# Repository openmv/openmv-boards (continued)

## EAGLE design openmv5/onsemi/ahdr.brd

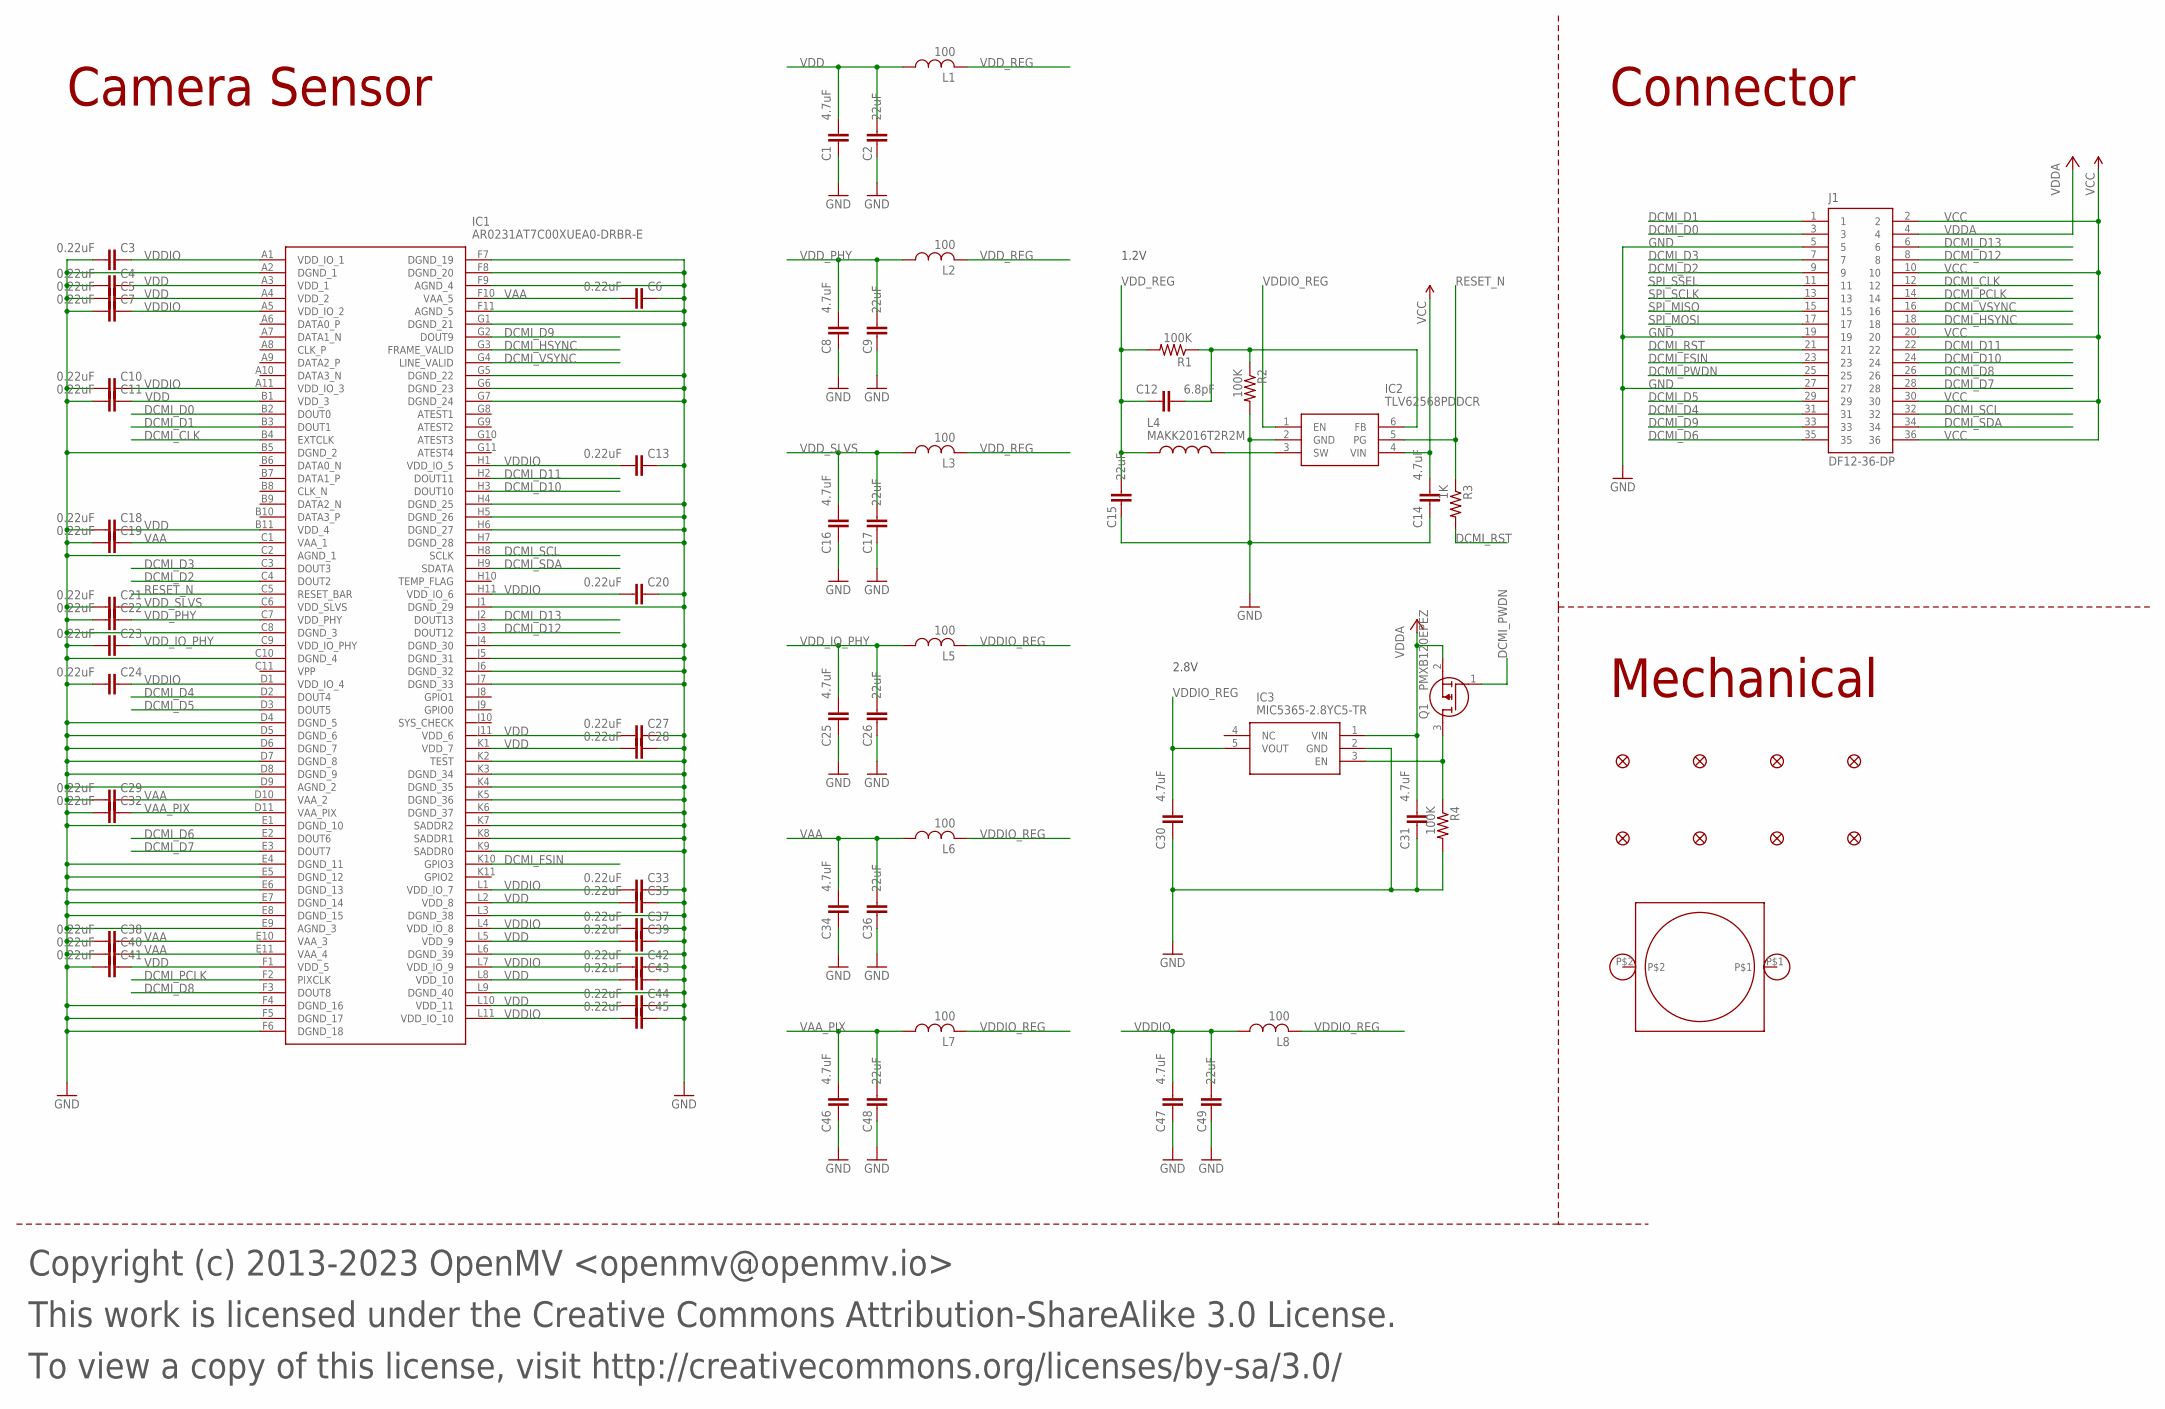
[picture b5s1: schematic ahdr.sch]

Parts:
C1, C8, C14, C16, C25, C30, C31, C34, C46, C47: 4.7uF; 0402; MPN JMK105BBJ475MV-F
C2, C9, C15, C17, C26, C36, C48, C49: 22uF; 0805; MPN CL21A226MQQNNNE
C3, C4, C5, C6, C7, C10, C11, C13, C18, C19, C20, C21, C22, C23, C24, C27, C28, C29, C32, C33, C35, C37, C38, C39, C40, C41, C42, C43, C44, C45: 0.22uF; C0201; MPN GRM033R60J224ME15D
C12: 6.8pF; 0402; MPN GRM1555C1H6R8DA01D
FD1, FD2, FD3, FD4, FD5, FD6, FD7, FD8: FIDUCIAL1X2; FIDUCIAL-1X2
H1: LENSMOUNT20MM; LENSMOUNT-20MM
IC1: AR0231AT7C00XUEA0-DRBR-E; BGA121C80P11X11_1100X1000X155; MPN AR0231AT7C00XUEA0-DPBR
IC2: TLV62568PDDCR; SOT95P280X110-6N; MPN TLV62568PDDCR
IC3: MIC5365-2.8YC5-TR; SOT65P210X110-5N; MPN MIC5365-2.8YC5-TR
J1: DF12-36-DP; MPN DF12NB(3.0)-36DP-0.5V(51)
L1, L2, L3, L5, L6, L7, L8: 100; 0402; MPN MFBM1V1005-101-R
L4: MAKK2016T2R2M; INDC2016X100N; MPN MAKK2016T2R2M
Q1: PMXB120EPEZ; MPN PMXB120EPEZ
R1, R2, R4: 100K; R0402; MPN AC0402FR-07100KL
R3: 1K; R0402; MPN CRCW04021K00FKEDC

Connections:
DCMI_CLK: IC1.B4 (EXTCLK), J1.12
DCMI_D0: IC1.B2 (DOUT0), J1.3
DCMI_D1: IC1.B3 (DOUT1), J1.1
DCMI_D2: IC1.C4 (DOUT2), J1.9
DCMI_D3: IC1.C3 (DOUT3), J1.7
DCMI_D4: IC1.D2 (DOUT4), J1.31
DCMI_D5: IC1.D3 (DOUT5), J1.29
DCMI_D6: IC1.E2 (DOUT6), J1.35
DCMI_D7: IC1.E3 (DOUT7), J1.28
DCMI_D8: IC1.F3 (DOUT8), J1.26
DCMI_D9: IC1.G2 (DOUT9), J1.33
DCMI_D10: IC1.H3 (DOUT10), J1.24
DCMI_D11: IC1.H2 (DOUT11), J1.22
DCMI_D12: IC1.J3 (DOUT12), J1.8
DCMI_D13: IC1.J2 (DOUT13), J1.6
DCMI_FSIN: IC1.K10 (GPIO3), J1.23
DCMI_HSYNC: IC1.G3 (FRAME_VALID), J1.18
DCMI_PCLK: IC1.F2 (PIXCLK), J1.14
DCMI_PWDN: J1.25, Q1.1 (G)
DCMI_PWDN_INT: IC3.3 (EN), Q1.3 (D), R4.1
DCMI_RST: J1.21, R3.2
DCMI_SCL: IC1.H8 (SCLK), J1.32
DCMI_SDA: IC1.H9 (SDATA), J1.34
DCMI_VSYNC: IC1.G4 (LINE_VALID), J1.16
FB: C12.2, IC2.6 (FB), R1.1, R2.1
GND: C1.1, C2.1, C3.2, C4.2, C5.2, C6.1, C7.2, C8.1, C9.1, C10.2, C11.2, C13.1, C14.1, C15.1, C16.1, C17.1, C18.2, C19.2, C20.1, C21.2, C22.2, C23.2, C24.2, C25.1, C26.1, C27.1, C28.1, C29.2, C30.1, C31.1, C32.2, C33.1, C34.1, C35.1, C36.1, C37.1, C38.2, C39.1, C40.2, C41.2, C42.1, C43.1, C44.1, C45.1, C46.1, C47.1, C48.1, C49.1, IC1.A2 (DGND_1), IC1.B5 (DGND_2), IC1.C2 (AGND_1), IC1.C8 (DGND_3), IC1.C10 (DGND_4), IC1.D4 (DGND_5), IC1.D5 (DGND_6), IC1.D6 (DGND_7), IC1.D7 (DGND_8), IC1.D8 (DGND_9), IC1.D9 (AGND_2), IC1.E1 (DGND_10), IC1.E4 (DGND_11), IC1.E5 (DGND_12), IC1.E6 (DGND_13), IC1.E7 (DGND_14), IC1.E8 (DGND_15), IC1.E9 (AGND_3), IC1.F4 (DGND_16), IC1.F5 (DGND_17), IC1.F6 (DGND_18), IC1.F7 (DGND_19), IC1.F8 (DGND_20), IC1.F9 (AGND_4), IC1.F11 (AGND_5), IC1.G1 (DGND_21), IC1.G5 (DGND_22), IC1.G6 (DGND_23), IC1.G7 (DGND_24), IC1.H4 (DGND_25), IC1.H5 (DGND_26), IC1.H6 (DGND_27), IC1.H7 (DGND_28), IC1.J1 (DGND_29), IC1.J4 (DGND_30), IC1.J5 (DGND_31), IC1.J6 (DGND_32), IC1.J7 (DGND_33), IC1.K2 (TEST), IC1.K3 (DGND_34), IC1.K4 (DGND_35), IC1.K5 (DGND_36), IC1.K6 (DGND_37), IC1.K7 (SADDR2), IC1.K8 (SADDR1), IC1.K9 (SADDR0), IC1.L3 (DGND_38), IC1.L6 (DGND_39), IC1.L9 (DGND_40), IC2.2 (GND), IC3.2 (GND), J1.5, J1.19, J1.27, R2.2, R4.2
RESET_N: IC1.C5 (RESET_BAR), IC2.5 (PG), R3.1
SPI_MISO: J1.15
SPI_MOSI: J1.17
SPI_SCLK: J1.13
SPI_SSEL: J1.11
SW: IC2.3 (SW), L4.2
VAA: C6.2, C19.1, C29.1, C34.2, C36.2, C38.1, C40.1, IC1.C1 (VAA_1), IC1.D10 (VAA_2), IC1.E10 (VAA_3), IC1.E11 (VAA_4), IC1.F10 (VAA_5), L6.1
VAA_PIX: C32.1, C46.2, C48.2, IC1.D11 (VAA_PIX), L7.1
VCC: C14.2, IC2.4 (VIN), J1.2, J1.10, J1.20, J1.30, J1.36
VDD: C1.2, C2.2, C4.1, C5.1, C11.1, C18.1, C27.2, C28.2, C35.2, C39.2, C41.1, C43.2, C44.2, IC1.A3 (VDD_1), IC1.A4 (VDD_2), IC1.B1 (VDD_3), IC1.B11 (VDD_4), IC1.F1 (VDD_5), IC1.J11 (VDD_6), IC1.K1 (VDD_7), IC1.L2 (VDD_8), IC1.L5 (VDD_9), IC1.L8 (VDD_10), IC1.L10 (VDD_11), L1.1
VDDA: C31.2, IC3.1 (VIN), J1.4, Q1.2 (S)
VDDIO: C3.1, C7.1, C10.1, C13.2, C20.2, C24.1, C33.2, C37.2, C42.2, C45.2, C47.2, C49.2, IC1.A1 (VDD_IO_1), IC1.A5 (VDD_IO_2), IC1.A11 (VDD_IO_3), IC1.D1 (VDD_IO_4), IC1.H1 (VDD_IO_5), IC1.H11 (VDD_IO_6), IC1.L1 (VDD_IO_7), IC1.L4 (VDD_IO_8), IC1.L7 (VDD_IO_9), IC1.L11 (VDD_IO_10), L8.1
VDDIO_REG: C30.2, IC2.1 (EN), IC3.5 (VOUT), L5.2, L6.2, L7.2, L8.2
VDD_IO_PHY: C23.1, C25.2, C26.2, IC1.C9 (VDD_IO_PHY), L5.1
VDD_PHY: C8.2, C9.2, C22.1, IC1.C7 (VDD_PHY), L2.1
VDD_REG: C12.1, C15.2, L1.2, L2.2, L3.2, L4.1, R1.2
VDD_SLVS: C16.2, C17.2, C21.1, IC1.C6 (VDD_SLVS), L3.1

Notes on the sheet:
Copyright (c) 2013-2023 OpenMV <openmv@openmv.io>
This work is licensed under the Creative Commons Attribution-ShareAlike 3.0 License.
To view a copy of this license, visit http://creativecommons.org/licenses/by-sa/3.0/
Camera Sensor
Mechanical
Connector
1.2V
2.8V

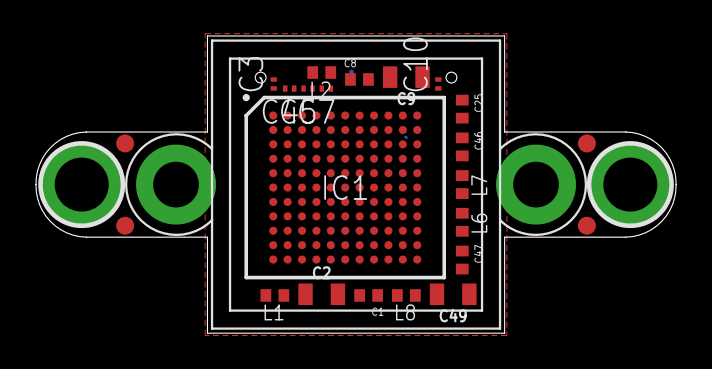
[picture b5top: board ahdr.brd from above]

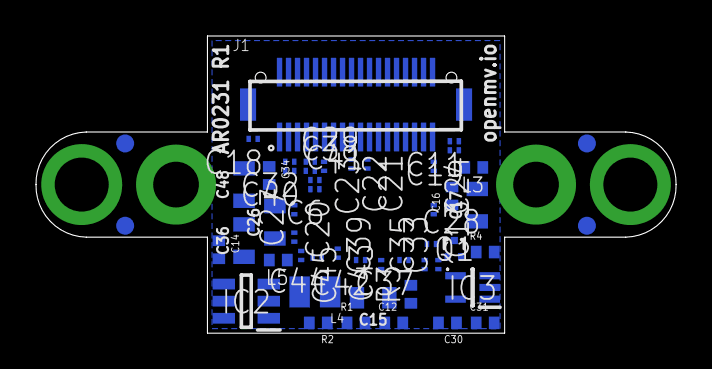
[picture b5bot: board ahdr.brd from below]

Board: 6 copper layers, 35.6 x 16.5 mm, 75 parts (51 on the bottom side), 39 nets.

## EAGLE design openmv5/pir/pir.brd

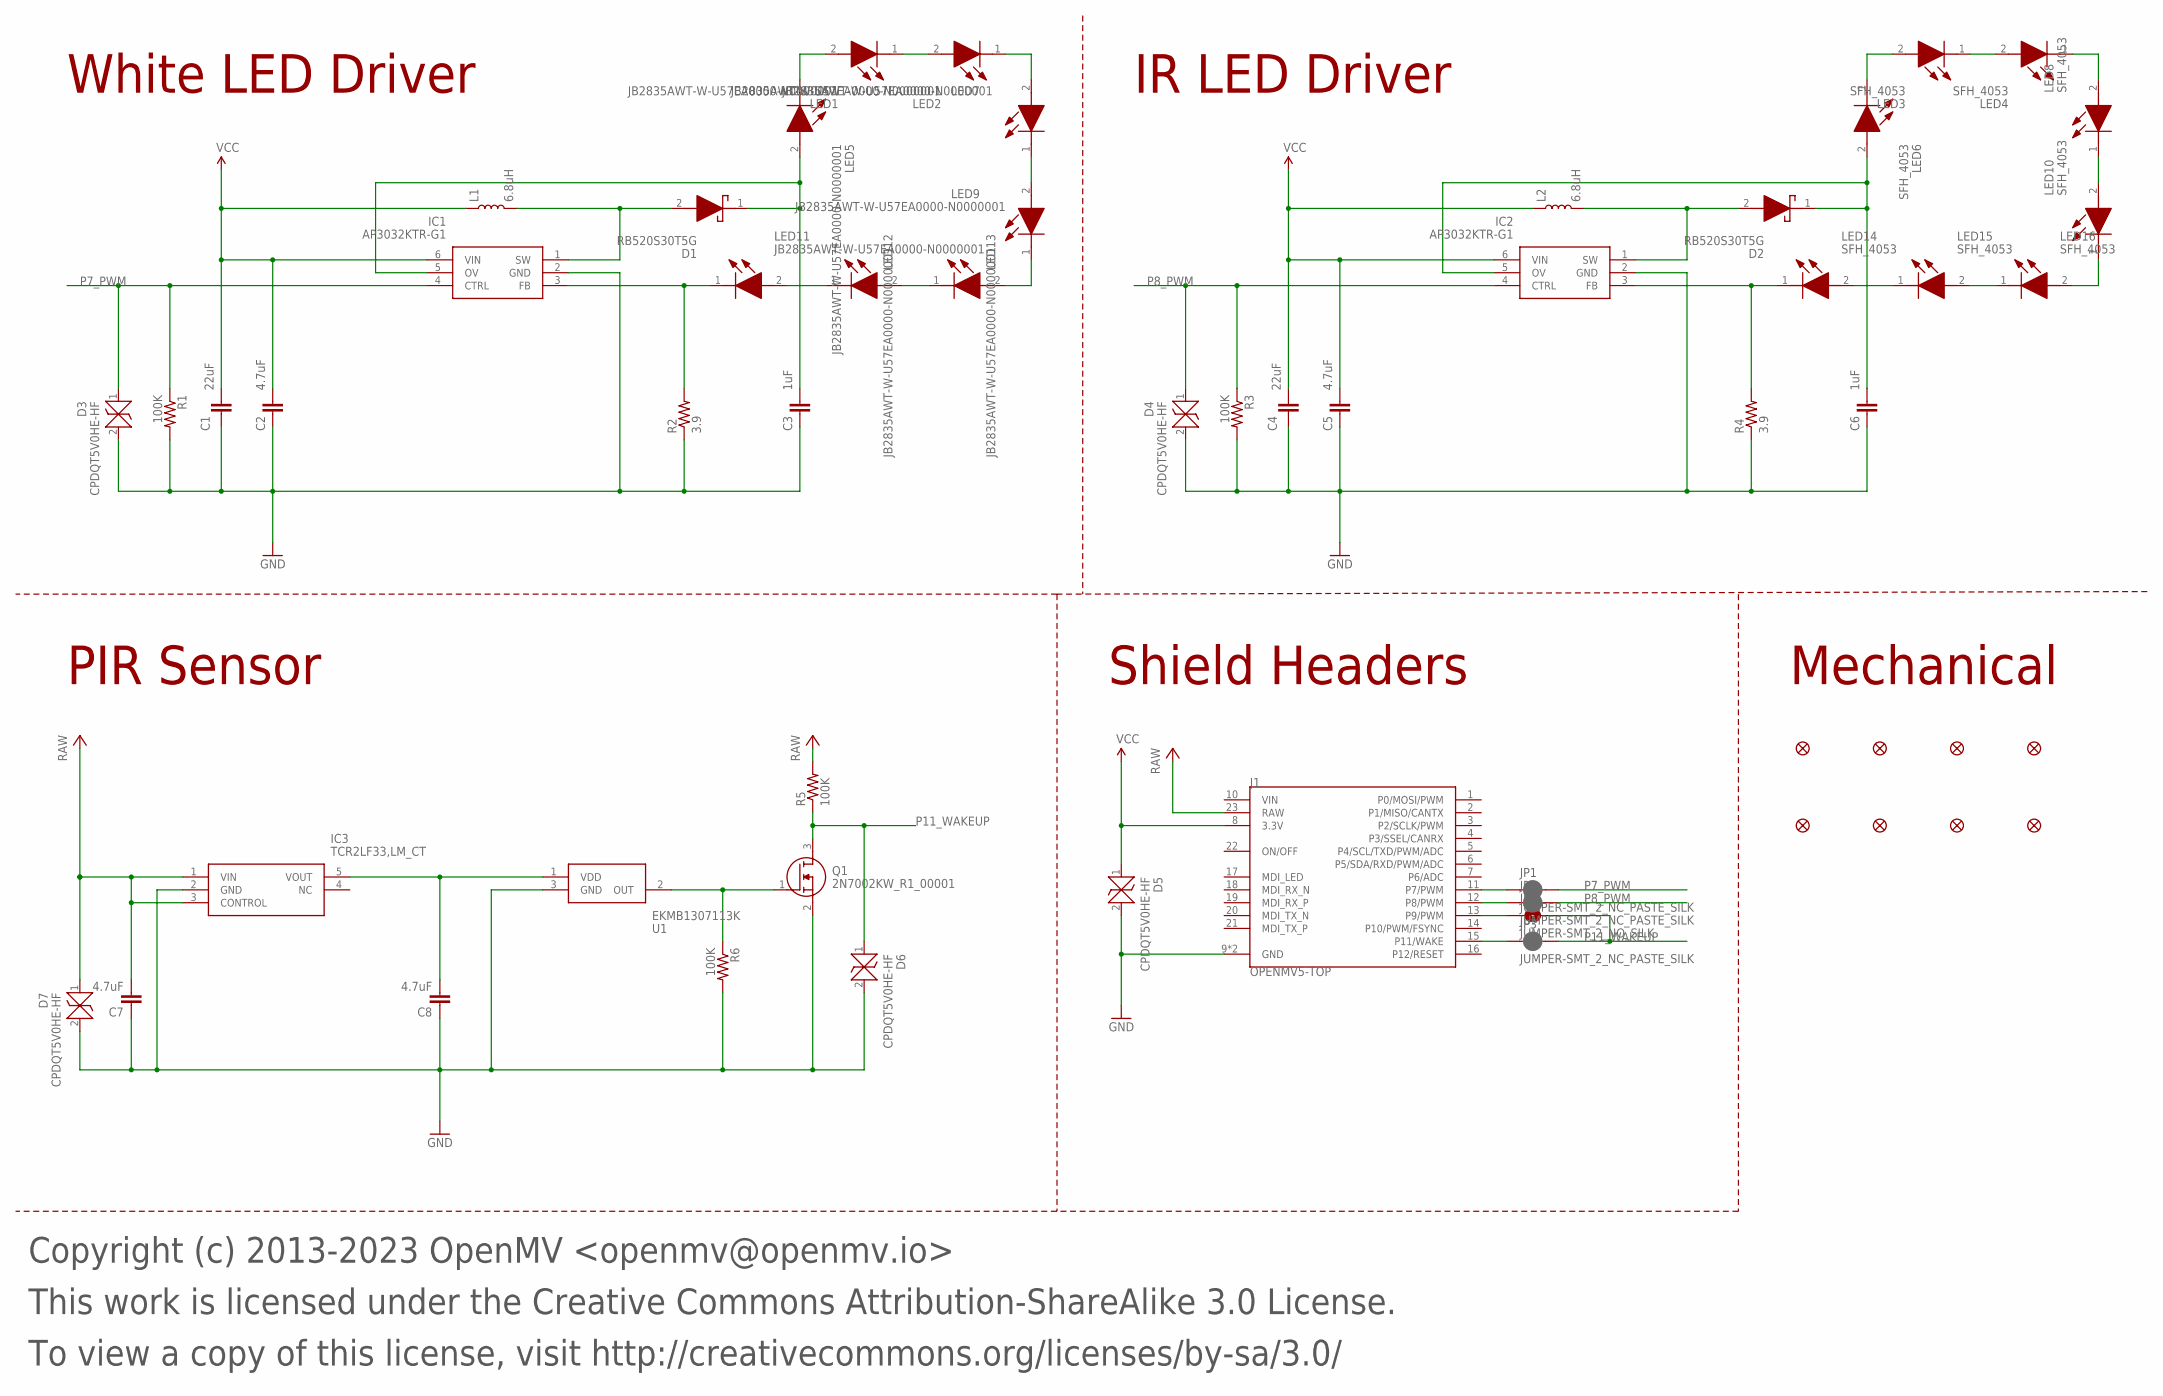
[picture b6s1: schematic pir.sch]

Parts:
C1, C4: 22uF; 0805; MPN CL21A226MQQNNNE
C2, C5, C7, C8: 4.7uF; 0402-CAP; MPN JMK105BBJ475MV-F
C3, C6: 1uF; 0402-CAP; MPN GRM155R61H105KE05D
D1, D2: RB520S30T5G; SODFL1608X70N; MPN RB520S30T5G
D3, D4, D5, D6, D7: CPDQT5V0HE-HF; CPDQT5V0HEHF; MPN CPDQT5V0HE-HF
FD1, FD2, FD3, FD4, FD5, FD6, FD7, FD8: FIDUCIAL1X2; FIDUCIAL-1X2
IC1, IC2: AP3032KTR-G1; SOT95P280X145-6N; MPN AP3032KTR-G1
IC3: TCR2LF33,LM_CT; TCR2LF33LMCT; MPN TCR2LF33,LM(CT
J1: OPENMV5-TOP
JP1, JP2, JP3: JUMPER-SMT_2_NC_PASTE_SILK; SMT-JUMPER_2_NC_PASTE_SILK
JP4: JUMPER-SMT_2_NO_SILK; SMT-JUMPER_2_NO_SILK
L1, L2: 6.8uH; 0805; MPN MLZ2012M6R8WT000
LED1, LED2, LED5, LED7, LED9, LED11, LED12, LED13: JB2835AWT-W-U57EA0000-N0000001; JB2835AWTWU57EA0000N0000001; MPN JB2835AWT-W-U57EA0000-N0000001
LED3, LED4, LED6, LED8, LED10, LED14, LED15, LED16: SFH_4053; LEDC1005X55N; MPN SFH 4053
Q1: 2N7002KW_R1_00001; SOT65P210X110-3N; MPN 2N7002KW_R1_00001
R1, R3, R5, R6: 100K; 0402-RES; MPN AC0402FR-07100KL
R2, R4: 3.9; R2512; MPN 35203R9JT
U1: EKMB1307113K; EKMB1304111K; MPN EKMB1307113K

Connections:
GND: C1.1, C2.1, C3.1, C4.1, C5.1, C6.1, C7.1, C8.1, D3.2, D4.2, D5.2, D6.2, D7.2, IC1.2 (GND), IC2.2 (GND), IC3.2 (GND), J1.9 (GND), J1.24 (GND), Q1.2 (S), R1.2, R2.1, R3.2, R4.1, R6.2, U1.3 (GND)
I1: LED3.2 (A), LED6.1 (K)
I2: LED3.1 (K), LED4.2 (A)
I3: LED4.1 (K), LED8.2 (A)
I4: LED8.1 (K), LED10.2 (A)
I5: LED10.1 (K), LED16.2 (A)
I6: LED15.2 (A), LED16.1 (K)
I7: LED14.2 (A), LED15.1 (K)
IFB: IC2.3 (FB), LED14.1 (K), R4.2
IOV: C6.2, D2.1 (K), IC2.5 (OV), LED6.2 (A)
ISW: D2.2 (A), IC2.1 (SW), L2.2
OUT: Q1.1 (G), R6.1, U1.2 (OUT)
P7_PWM: D3.1, IC1.4 (CTRL), JP1.2, R1.1
P7_PWM_INT: J1.11 (P7/PWM), JP1.1
P8_PWM: D4.1, IC2.4 (CTRL), JP2.2, R3.1
P8_PWM_INT: J1.12 (P8/PWM), JP2.1
P11_WAKEUP: D6.1, JP3.2, JP4.2, Q1.3 (D), R5.1
P11_WAKEUP_INT: J1.15 (P11/WAKE), JP3.1
P11_WAKEUP_INT_2: J1.13 (P9/PWM), JP4.1
RAW: C7.2, D7.1, IC3.1 (VIN), IC3.3 (CONTROL), J1.23 (RAW), R5.2
VCC: C1.2, C2.2, C4.2, C5.2, D5.1, IC1.6 (VIN), IC2.6 (VIN), J1.8 (3.3V), L1.1, L2.1
VDD: C8.2, IC3.5 (VOUT), U1.1 (VDD)
W1: LED1.2 (A), LED5.1 (K)
W2: LED1.1 (K), LED2.2 (A)
W3: LED2.1 (K), LED7.2 (A)
W4: LED7.1 (K), LED9.2 (A)
W5: LED9.1 (K), LED13.2 (A)
W6: LED12.2 (A), LED13.1 (K)
W7: LED11.2 (A), LED12.1 (K)
WFB: IC1.3 (FB), LED11.1 (K), R2.2
WOV: C3.2, D1.1 (K), IC1.5 (OV), LED5.2 (A)
WSW: D1.2 (A), IC1.1 (SW), L1.2

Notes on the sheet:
Copyright (c) 2013-2023 OpenMV <openmv@openmv.io>
This work is licensed under the Creative Commons Attribution-ShareAlike 3.0 License.
To view a copy of this license, visit http://creativecommons.org/licenses/by-sa/3.0/
White LED Driver
PIR Sensor
Mechanical
IR LED Driver
Shield Headers

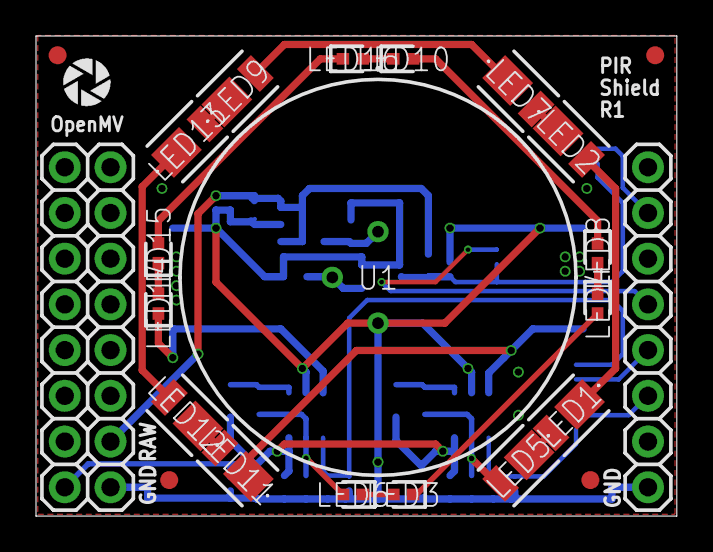
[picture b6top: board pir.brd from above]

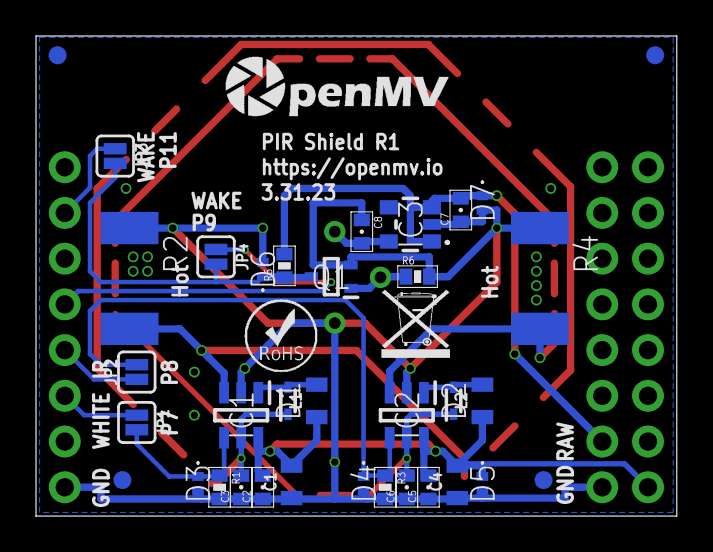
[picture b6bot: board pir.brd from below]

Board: 2 copper layers, 35.6 x 26.7 mm, 61 parts (38 on the bottom side), 32 nets.

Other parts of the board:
U$1: WEEE
U$2: ROHS
U$3: OMV-LOGO
U$9: OPENMV-LOGO
